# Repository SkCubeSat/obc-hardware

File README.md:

# obc-hardware
Hardware based around the pocket beagle to run flight software

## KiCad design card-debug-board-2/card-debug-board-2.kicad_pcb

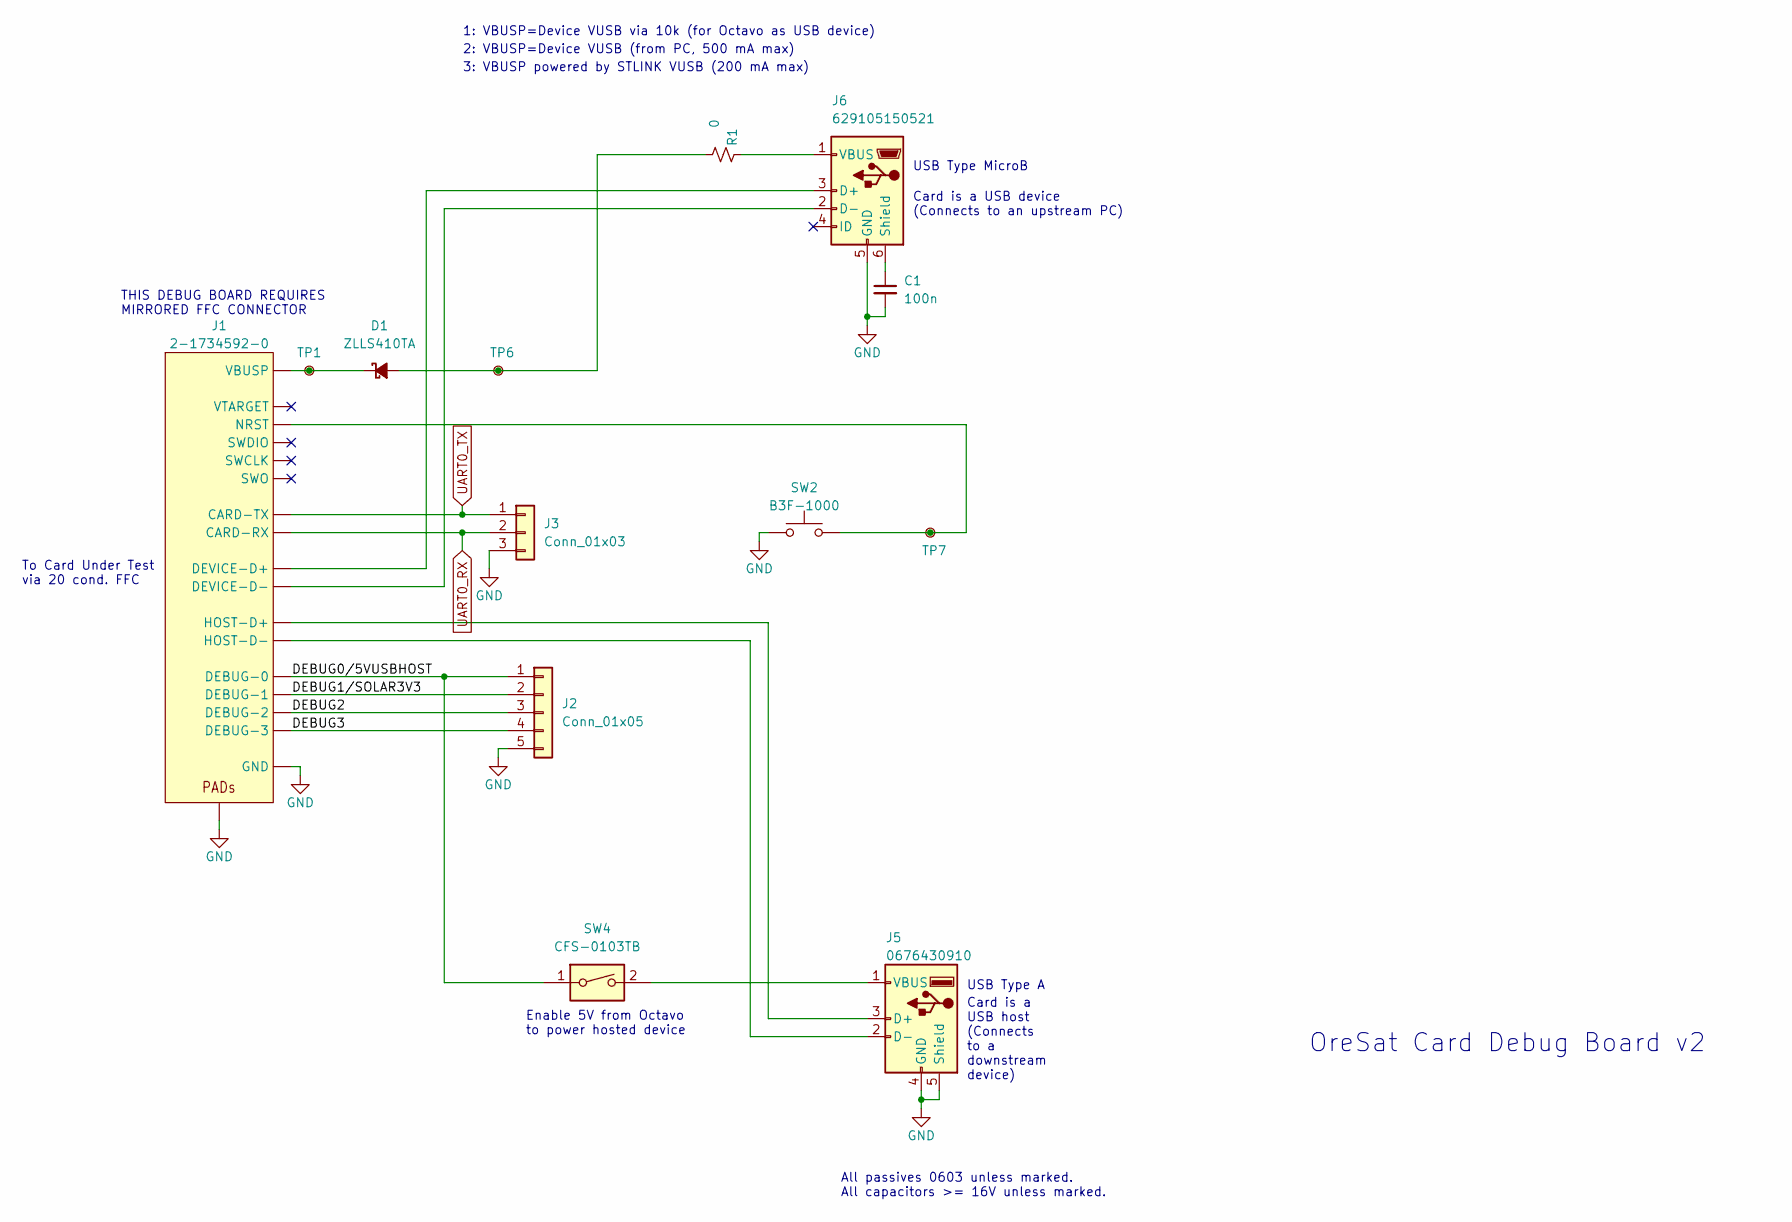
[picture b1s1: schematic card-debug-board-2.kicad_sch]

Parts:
C1: 100n; C_0603_1608Metric
D1: ZLLS410TA; D_SOD-323; MPN Diodes Inc
J1: 2-1734592-0; J-TE_2-1734592-0_FFC_MIRRORED; MPN 2-1734592-0
J2: Conn_01x05; PinHeader_1x05_P2.54mm_Vertical
J3: Conn_01x03; PinHeader_1x03_P2.54mm_Vertical
J5: 0676430910; USB_A_Molex_67643_Horizontal; MPN 0676430910
J6: 629105150521; USB_Micro-B_Wuerth_629105150521_CircularHoles; MPN 629105150521
R1: 0; R_0603_1608Metric
SW2: B3F-1000; SW_PUSH_6mm; MPN Omron Electronics
SW4: CFS-0103TB; SW_DIP_SPSTx01_Slide_Copal_CHS-01B_W7.62mm_P1.27mm; MPN CFS-0103TB
TP1, TP6, TP7: TestPoint-MinTH

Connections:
/DEBUG0/5VUSBHOST: J1.17 (DEBUG-0), J2.1, SW4.1
/DEBUG1/SOLAR3V3: J1.18 (DEBUG-1), J2.2
/DEBUG2: J1.19 (DEBUG-2), J2.3
/DEBUG3: J1.20 (DEBUG-3), J2.4
GND: C1.2, J1.3 (GND), J1.6 (GND), J1.9 (GND), J1.PAD1 (PAD), J1.PAD2 (PAD), J2.5, J3.3, J5.4 (GND), J5.5 (Shield), J6.5 (GND), SW2.1
unnamed: D1.2 (A), R1.2, TP6.1 (1_1)
unnamed: D1.1 (K), J1.1 (VBUSP), J1.2 (VBUSP), TP1.1 (1_1)
unnamed: J1.4 (DEVICE-D+), J6.3 (D+)
unnamed: J1.5 (DEVICE-D-), J6.2 (D-)
unnamed: J1.7 (HOST-D+), J5.3 (D+)
unnamed: J1.8 (HOST-D-), J5.2 (D-)
unnamed: J1.10 (NRST), SW2.2, TP7.1 (1_1)
unnamed: J5.1 (VBUS), SW4.2
unnamed: C1.1, J6.6 (Shield)
unnamed: J6.1 (VBUS), R1.1
UART0_RX: J1.12 (CARD-RX), J3.2
UART0_TX: J1.13 (CARD-TX), J3.1

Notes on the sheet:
2: VBUSP=Device VUSB (from PC, 500 mA max)
USB Type MicroB
To Card Under Test via 20 cond. FFC
OreSat Card Debug Board v2
USB Type A
Card is a USB host (Connects to a downstream device)
All passives 0603 unless marked. All capacitors >= 16V unless marked.
THIS DEBUG BOARD REQUIRES MIRRORED FFC CONNECTOR
1: VBUSP=Device VUSB via 10k (for Octavo as USB device)
Card is a USB device (Connects to an upstream PC)
3: VBUSP powered by STLINK VUSB (200 mA max)
Enable 5V from Octavo to power hosted device

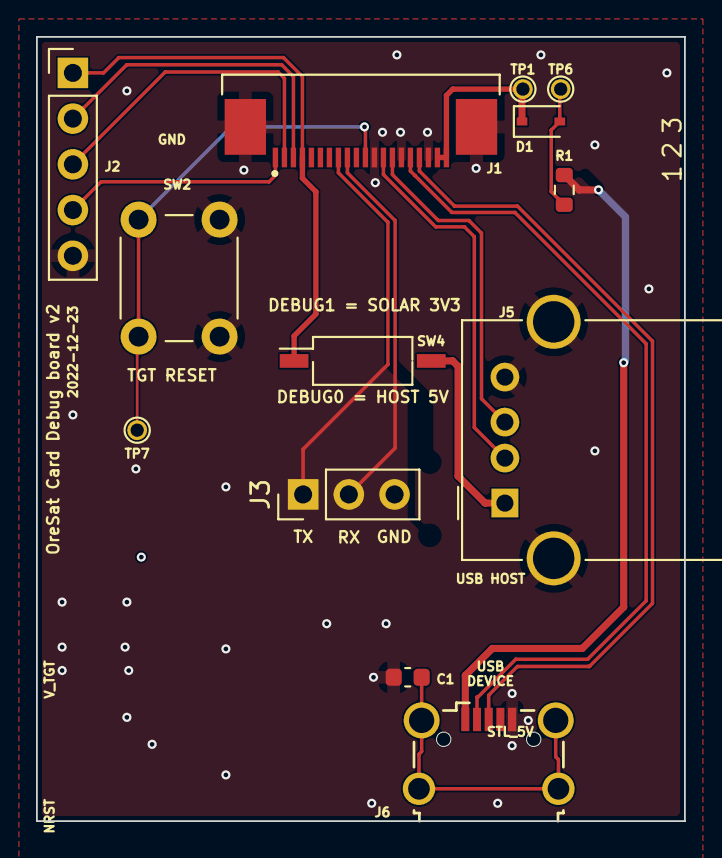
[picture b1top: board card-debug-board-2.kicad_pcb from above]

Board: 2 copper layers, 36.0 x 43.6 mm, 13 parts (0 on the bottom side), 17 nets.

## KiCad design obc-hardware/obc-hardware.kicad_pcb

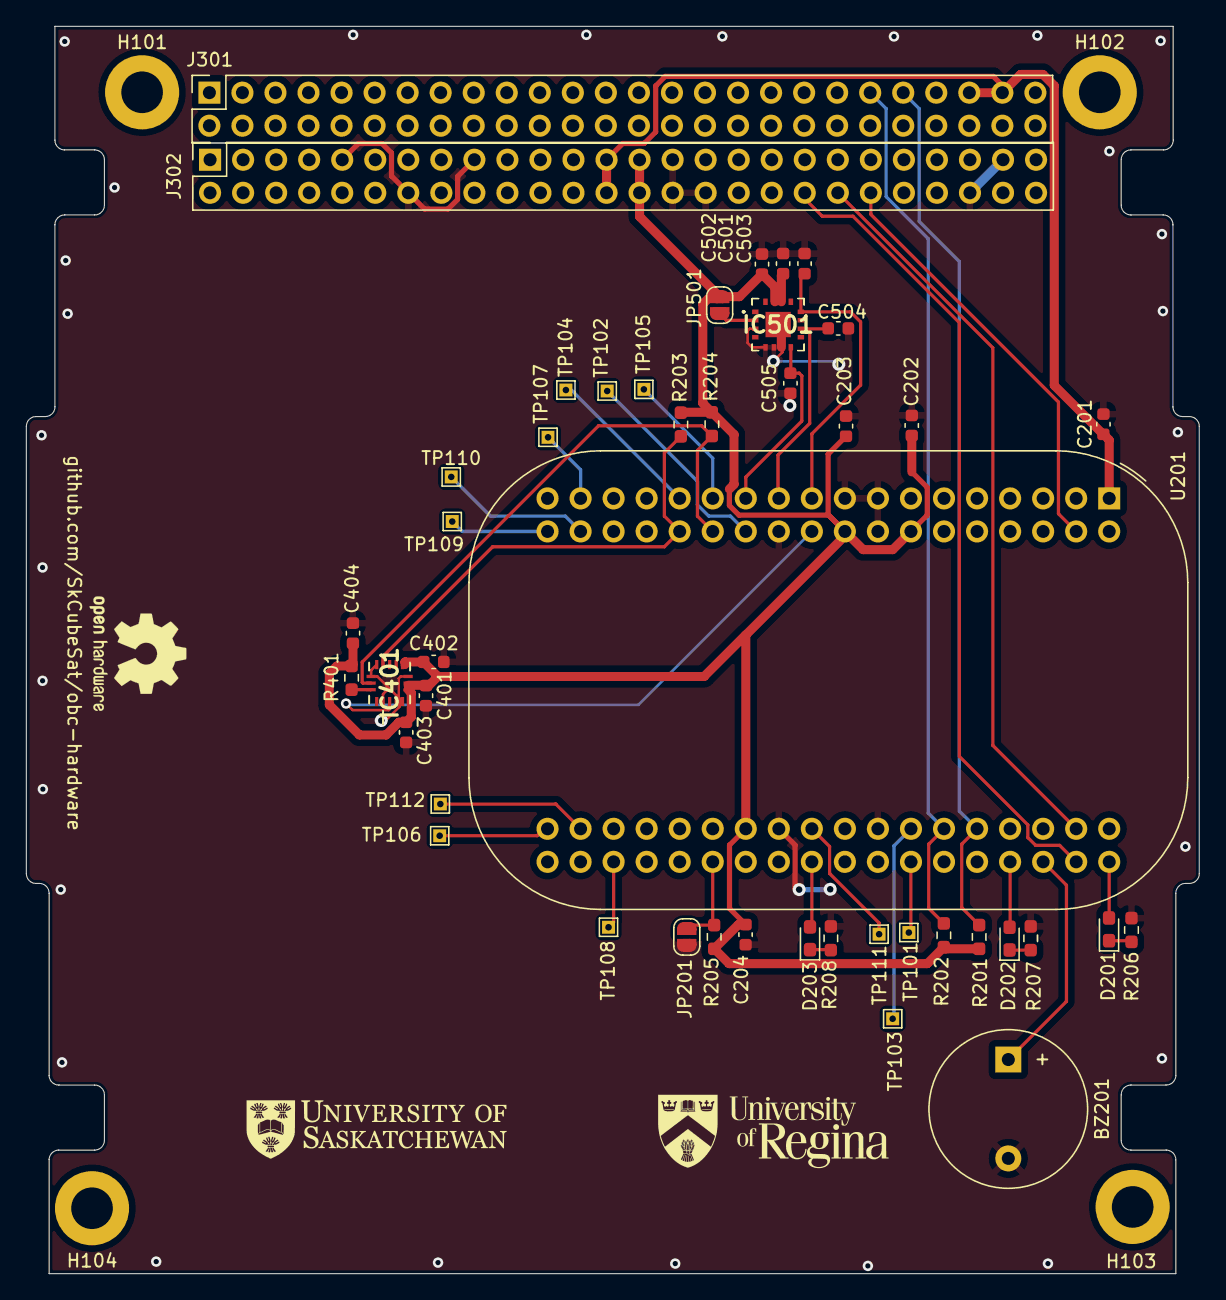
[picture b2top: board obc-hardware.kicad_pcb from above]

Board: 2 copper layers, 90.2 x 95.9 mm, 49 parts (0 on the bottom side), 36 nets.

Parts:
BZ201: Buzzer; Buzzer_12x9.5RM7.6
C201, C202, C203, C204, C401, C402, C403, C404, C501, C502: 0.1u; C_0603_1608Metric
C503, C504, C505: 4.7uF; C_0603_1608Metric
D201, D202, D203: LED; LED_0603_1608Metric_Pad1.05x0.95mm_HandSolder
H101, H102, H103, H104: MountingHole; MountingHole_3.2mm_M3_ISO7380_Pad
IC401: H3LIS200DLTR; LGA16R50P3X5_300X300X100
IC501: ADXL335BCPZ
J301, J302: Conn_02x26_Odd_Even; PinSocket_2x26_P2.54mm_Vertical
JP201, JP501: Jumper_2_Open; SolderJumper-2_P1.3mm_Open_RoundedPad1.0x1.5mm
R201, R202, R203, R204: 2k; R_0603_1608Metric_Pad0.98x0.95mm_HandSolder
R205, R206, R207, R208: 10k; R_0603_1608Metric_Pad0.98x0.95mm_HandSolder
R401: 0R; R_0603_1608Metric_Pad0.98x0.95mm_HandSolder
TP101, TP102, TP103, TP104, TP105, TP106, TP107, TP108, TP109, TP110, TP111, TP112: TestPoint; TestPoint_THTPad_1.0x1.0mm_Drill0.5mm
U201: PocketBeagle; BeagleBoard_PocketBeagle

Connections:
+3.3V: C202.1, C203.1, C204.1, C401.1, C402.1, C403.1, C404.1, C501.1, C502.1, IC401.1 (VDD_IO), IC401.14 (VDD), IC401.15 (RESERVED_2), IC501.14 (VS_1), IC501.15 (VS_2), J302.27, J302.28, JP501.1 (A), R201.1, R202.1, R203.1, R204.1, R205.1, R401.1, U201.14 (3.3V), U201.18 (AIN.VREF+), U201.59 (3.3V)
+5V: C201.1, J301.47, J301.49, J302.25, J302.26, U201.1 (VIN)
/AXXL/INT1: IC401.11 (INT_1), U201.20 (GPIO20)
/CSKB/H2-38: J302.38, U201.40 (GPIO58)
/CSKB/H2-40: J302.40, U201.39 (GPIO23)
/CSKB/H2-42: J302.42, U201.4 (GPIO89)
/IMU/XOUT: C503.1, IC501.12 (XOUT), U201.19 (AIN0(1.8V))
/IMU/YOUT: C504.1, IC501.10 (YOUT), U201.21 (AIN1(1.8V))
/IMU/ZOUT: C505.1, IC501.8 (ZOUT), U201.23 (AIN2(1.8V))
/Pocket Beagle/AIN3: TP105.1, U201.25 (AIN3(1.8V))
/Pocket Beagle/AIN4: TP104.1, U201.27 (AIN4(1.8V))
/Pocket Beagle/AIN5: TP106.1, U201.71 (AIN5(3.3V))
/Pocket Beagle/BAT.VIN: TP101.1, U201.50 (BAT.VIN)
/Pocket Beagle/GPIO26: TP110.1, U201.34 (GPIO26)
/Pocket Beagle/GPIO27: TP111.1, U201.55 (GPIO27)
/Pocket Beagle/GPIO45: TP112.1, U201.69 (GPIO45)
/Pocket Beagle/PRU0.1: TP107.1, U201.33 (PRU0.1)
/Pocket Beagle/PRU0.2: TP108.1, U201.68 (PRU0.2)
/Pocket Beagle/PWM0A: TP109.1, U201.36 (PWM0A)
/Pocket Beagle/VOUT-24: TP102.1, U201.24 (VOUT)
/Pocket Beagle/VOUT-49: TP103.1, U201.49 (VOUT)
GND: BZ201.2 (+), C201.2, C202.2, C203.2, C204.2, C401.2, C402.2, C403.2, C404.2, C501.2, C502.2, C503.2, C504.2, C505.2, IC401.5 (SPC), IC401.6 (GND_1), IC401.10 (RESERVED_1), IC401.12 (GND_2), IC401.13 (GND_3), IC401.16 (GND_4), IC501.3 (COM_1), IC501.5 (COM_2), IC501.6 (COM_3), IC501.7 (COM_4), IC501.17 (EP), J302.9, J302.14, J302.17, J302.29, J302.30, J302.32, J302.48, J302.49, JP201.1 (A), R206.2, R207.2, R208.2, U201.15 (GND), U201.16 (GND), U201.17 (AIN.VREF-), U201.22 (GND), U201.51 (GND), U201.57 (GND)
I2C1_SCL: J301.43, R201.2, U201.45 (I2C1.SCL)
I2C1_SDA: J301.41, R202.2, U201.47 (I2C1.SDA)
I2C2_SCL: IC401.4 (SCL), R203.2, U201.28 (I2C2.SCL)
I2C2_SDA: IC401.7 (SDA/SDI/SDO), R204.2, U201.26 (I2C2.SDA)
unnamed: BZ201.1 (-), U201.42 (GPIO57)
unnamed: D201.2 (A), U201.38 (GPIO59)
unnamed: D201.1 (K), R206.1
unnamed: D202.2 (A), U201.44 (GPIO60)
unnamed: D202.1 (K), R207.1
unnamed: D203.2 (A), U201.56 (GPIO64)
unnamed: D203.1 (K), R208.1
unnamed: IC401.8 (SDO/SA0), R401.2
unnamed: IC501.2 (ST), JP501.2 (B)
unnamed: JP201.2 (B), R205.2, U201.62 (~RESET)

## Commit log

2023-07-21 POC rev 1.0
2023-07-22 added GPIO for payload
2023-07-24 added test points
2023-07-25 push for production
2024-08-05 Added oresat debug board kicad files
2024-09-25 Modified debug board, removed several peripherals
2026-06-28 Added proper connector for UART and changed 10k ohm resistor on the VBUS line to 0 ohm
